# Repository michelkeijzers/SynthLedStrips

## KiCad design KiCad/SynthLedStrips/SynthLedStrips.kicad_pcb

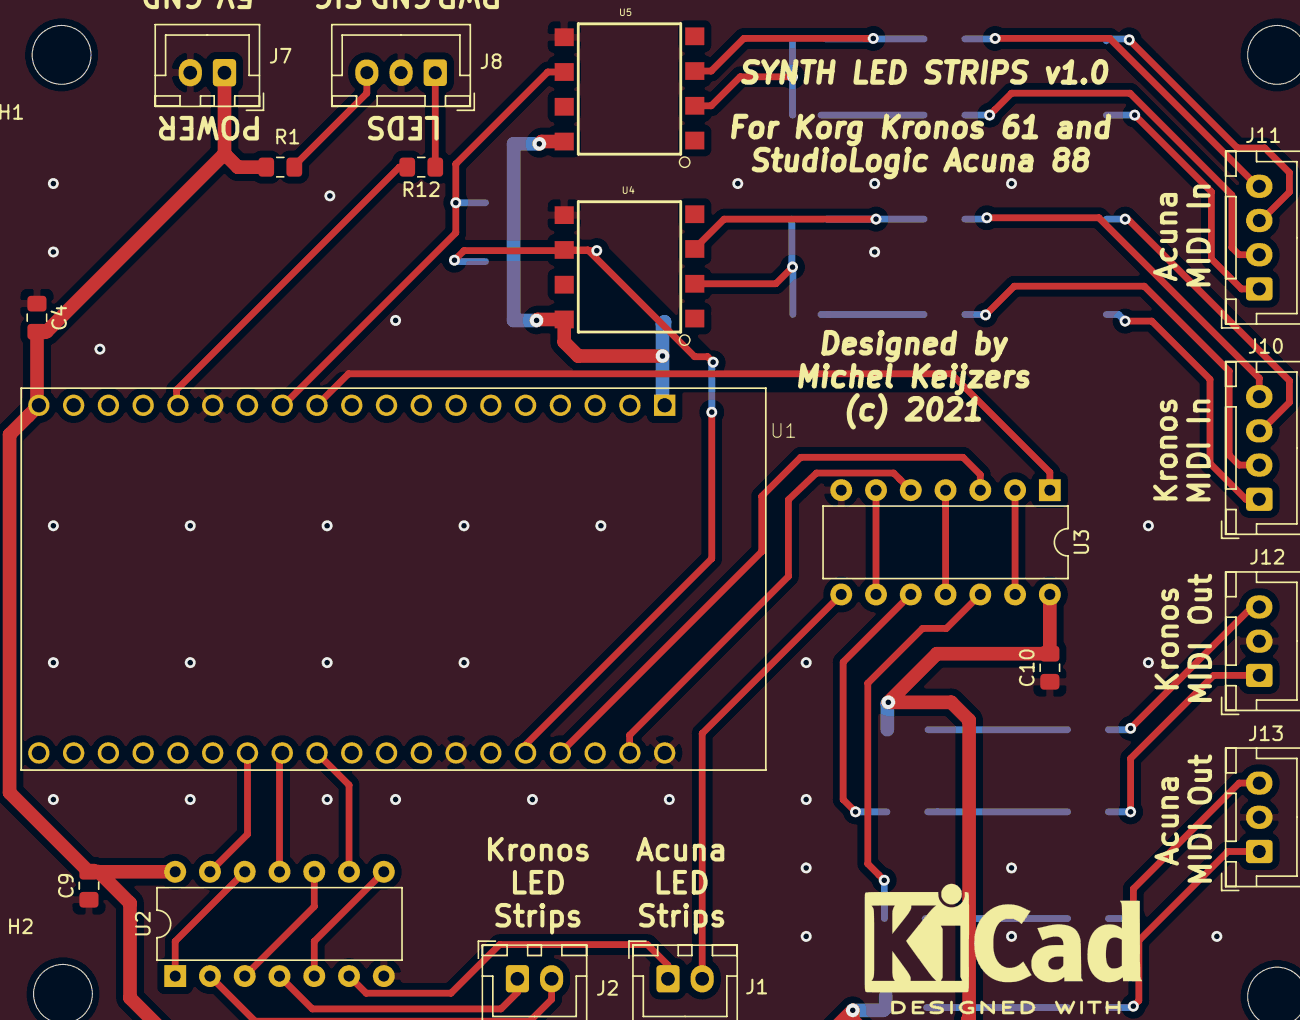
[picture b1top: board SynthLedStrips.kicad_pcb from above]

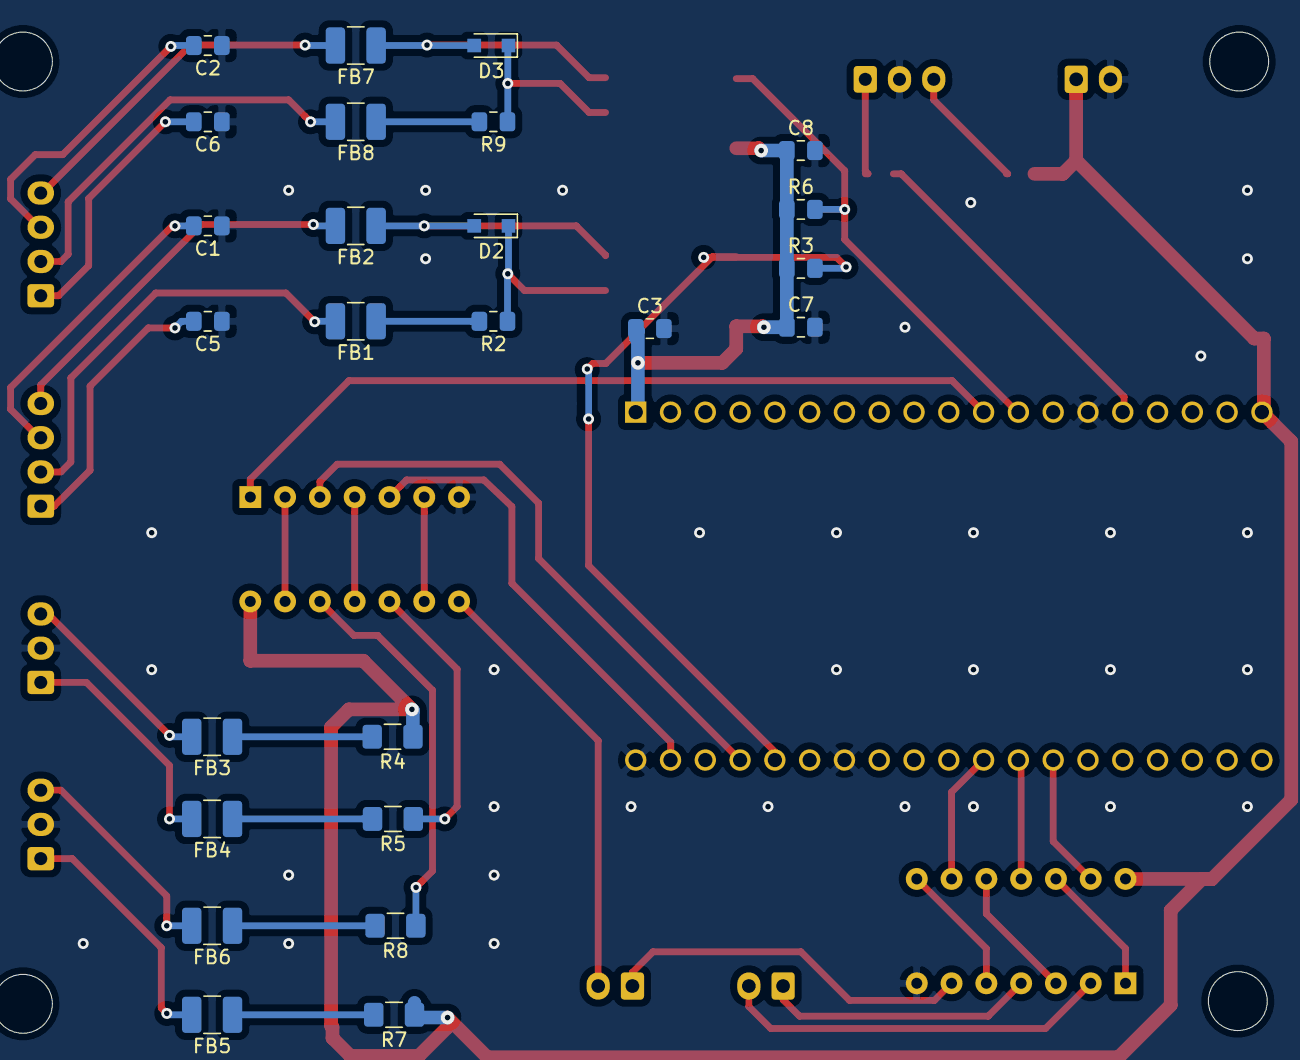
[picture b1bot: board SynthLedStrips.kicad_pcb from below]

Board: 2 copper layers, 47 parts (25 on the bottom side), 48 nets.

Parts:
C1, C2, C3, C4, C5, C6, C7, C8, C9, C10: 0.1uF; C_0805_2012Metric_Pad1.15x1.40mm_HandSolder
D2, D3: 1N4148; D_SOD-323_HandSoldering
FB1, FB2, FB3, FB4, FB5, FB6, FB7, FB8: 1K@100MHz; Fuse_1210_3225Metric_Pad1.42x2.65mm_HandSolder
H1, H2, H3, H4: MountingHole; MountingHole_4.3mm_M4
J1: XH Acuna LED Strips; JST_XH_B2B-XH-A_1x02_P2.50mm_Vertical
J2: XH Kronos LED Strips; JST_XH_B2B-XH-A_1x02_P2.50mm_Vertical
J7: XH Power; JST_XH_B2B-XH-A_1x02_P2.50mm_Vertical
J8: XH LEDs; JST_XH_B3B-XH-A_1x03_P2.50mm_Vertical
J10: XH Kronos MIDI In; JST_XH_B4B-XH-A_1x04_P2.50mm_Vertical
J11: XH Acuna In; JST_XH_B4B-XH-A_1x04_P2.50mm_Vertical
J12: XH Kronos MIDI Out; JST_XH_B3B-XH-A_1x03_P2.50mm_Vertical
J13: XH Acuna Out; JST_XH_B3B-XH-A_1x03_P2.50mm_Vertical
R1, R12: 330R; R_0805_2012Metric_Pad1.15x1.40mm_HandSolder
R2, R9: 220R; R_0805_2012Metric_Pad1.15x1.40mm_HandSolder
R3, R6: 10K; R_0805_2012Metric_Pad1.15x1.40mm_HandSolder
R4, R5, R7, R8: 220R 5% 0.25W; R_1206_3216Metric_Pad1.42x1.75mm_HandSolder
U1: ESP32-DEVKITC-32D; MODULE_ESP32-DEVKITC-32D
U2, U3: 74HC14; DIP-14_W7.62mm
U4, U5: 6N137; 8-SMD

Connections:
+3V3: C3.1, C7.1, C8.1, R3.1, R6.1, U1.1, U4.8, U5.8
+5V: C4.2, C9.2, C10.2, J7.1, R1.2, R4.1, R7.1, U1.19, U2.14, U3.14
/ACUNA_LED_STRIP_BACK: U1.21, U3.5
/ACUNA_LED_STRIP_FRONT: U1.30, U2.9
/ACUNA_MIDI_IN: R6.2, U1.12, U5.6
/ACUNA_MIDI_OUT: U1.11, U3.1
/KRONOS_LED_STRIP_BACK: U1.32, U2.13
/KRONOS_LED_STRIP_FRONT: U1.31, U2.11
/KRONOS_MIDI_IN: R3.2, U1.24, U4.6
/KRONOS_MIDI_OUT: U1.23, U3.3
/SIGNAL_LED: R12.2, U1.15
GND: C1.1, C2.1, C3.2, C4.1, C5.1, C6.1, C7.2, C8.2, C9.1, C10.1, J7.2, J8.2, J12.2, J13.2, U1.14, U1.20, U1.26, U2.7, U3.7, U4.5, U5.5
unnamed: C1.2, J10.3
unnamed: C2.2, J11.3
unnamed: C5.2, J10.1
unnamed: C6.2, J11.1
unnamed: J8.3, R1.1
unnamed: D2.1, R2.1, U4.2
unnamed: D2.2, FB2.1, U4.3
unnamed: D3.1, R9.1, U5.2
unnamed: D3.2, FB7.1, U5.3
unnamed: J8.1, R12.1
unnamed: FB1.1, R2.2
unnamed: FB1.2, J10.2
unnamed: FB2.2, J10.4
unnamed: FB3.1, R4.2
unnamed: FB3.2, J12.3
unnamed: FB4.1, R5.2
unnamed: FB4.2, J12.1
unnamed: FB5.1, R7.2
unnamed: FB5.2, J13.1
unnamed: FB6.1, R8.2
unnamed: FB6.2, J13.3
unnamed: FB7.2, J11.4
unnamed: FB8.1, R9.2
unnamed: FB8.2, J11.2
unnamed: J1.1, U2.6
unnamed: J1.2, U3.8
unnamed: J2.1, U2.4
unnamed: J2.2, U2.2
unnamed: R5.1, U3.10
unnamed: R8.1, U3.12
unnamed: U2.1, U2.12
unnamed: U2.5, U2.8
unnamed: U2.3, U2.10
unnamed: U3.6, U3.9
unnamed: U3.4, U3.11
unnamed: U3.2, U3.13

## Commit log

2021-02-25 Add .gitignore and .gitattributes.
2021-02-25 Add project files.
2021-02-25 First version
2021-02-25 First compile.
2021-02-28 Knightrider works
2021-03-02 MIDI initial part
2021-03-02 MidiKeyboard start
2021-03-04 Colors, time and speed for parameters
2021-03-04 Color changing
2021-03-05 Architectural changes/bug fixes
2021-03-07 Speed and Times
2021-03-08 colors, speed, times, MIDI On/off pattern changes
2021-03-08 Pattern classes and placement new.
2021-03-08 Pattern MIDI Note on/off, not working yet
2021-03-09 Fade MIDI note ON for MIDI note on/off pattern, next: Fade MIDI note OFF
2021-03-09 Fade time On/off working
2021-03-10 Rainbow color for Knight rider, math utils refactored, removed serial print.
2021-03-10 End of file empty lines cleanup
2021-03-11 Fixing patterns
2021-03-11 Fixed knight rider speeds
2021-03-15 Keys = # Back LEDs, various other changes
2021-03-16 Major refactoring
2021-03-16 Cleanup
2021-03-16 Current protection
2021-03-19 Galaxy color, although stuttering
2021-03-21 ESP32
2021-03-22 Removed Time and Speed enums
2021-03-22 Created MidiNote, removed counter.
2021-03-23 Fixed bug for uint8_t use for leds which can be higher than 128.
2021-03-26 Crash
2021-03-28 NULL -> nullptr
2021-03-28 Crash fixed, midi note on/off pattern still doesn't do anything
2021-03-29 Fixed sideways movement for MIDI note on/off pattern
2021-03-29 Changed most speeds to times.
2021-03-29 Cleaned up, removed empty destructors, constexpr
2021-04-01 Various, name change
2021-04-06 OTA changes and more.
2021-04-07 Midi Inject/MIDI channel
2021-04-07 Coped backup after wrong merge
2021-04-07 Bug fixed.
2021-04-12 config file
2021-04-21 Reading configuration
2021-04-22 Splits, Off and Knight Rider works again with configuration. MIDI note on/of has a bug (shows range instead of fading notes)
2021-04-29 Fixes regarding MIDI note on/off (still not working correctly), adding char to print.
2021-06-01 Fixed bug
2021-06-01 KiCad files
2021-06-09 KiCad project

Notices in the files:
KiCad/SynthLedStrips/SynthLedStrips.kicad_pcb:
(c) 2021
